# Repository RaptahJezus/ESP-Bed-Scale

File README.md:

ESP Powered Bed Occupancy Sensor

Uses HX711 chip and 4 load cells 

[Load Cells + HX711](https://www.ebay.com/itm/4pcs-50KG-Body-Load-Cell-Resistance-Strain-Weight-Sensor-HX711-AD-Module/182899653153)

Note: Load cells require a bracket that supports the edge, while allowing the middle portion to deflect. Included is "half_bridge_load_sensor_holder-original.stl" which can be 3D printed. I used ABS plastic for mine and it works well.

Load cell bracket design courtesy of linorics on [Thingverse](https://www.thingiverse.com/thing:2486831).

Set up WiFi and MQTT settings in Firmware/include/config.h. Example file is included

Programmed using VSCode + PlatformIO. Schematic designed in EagleCAD

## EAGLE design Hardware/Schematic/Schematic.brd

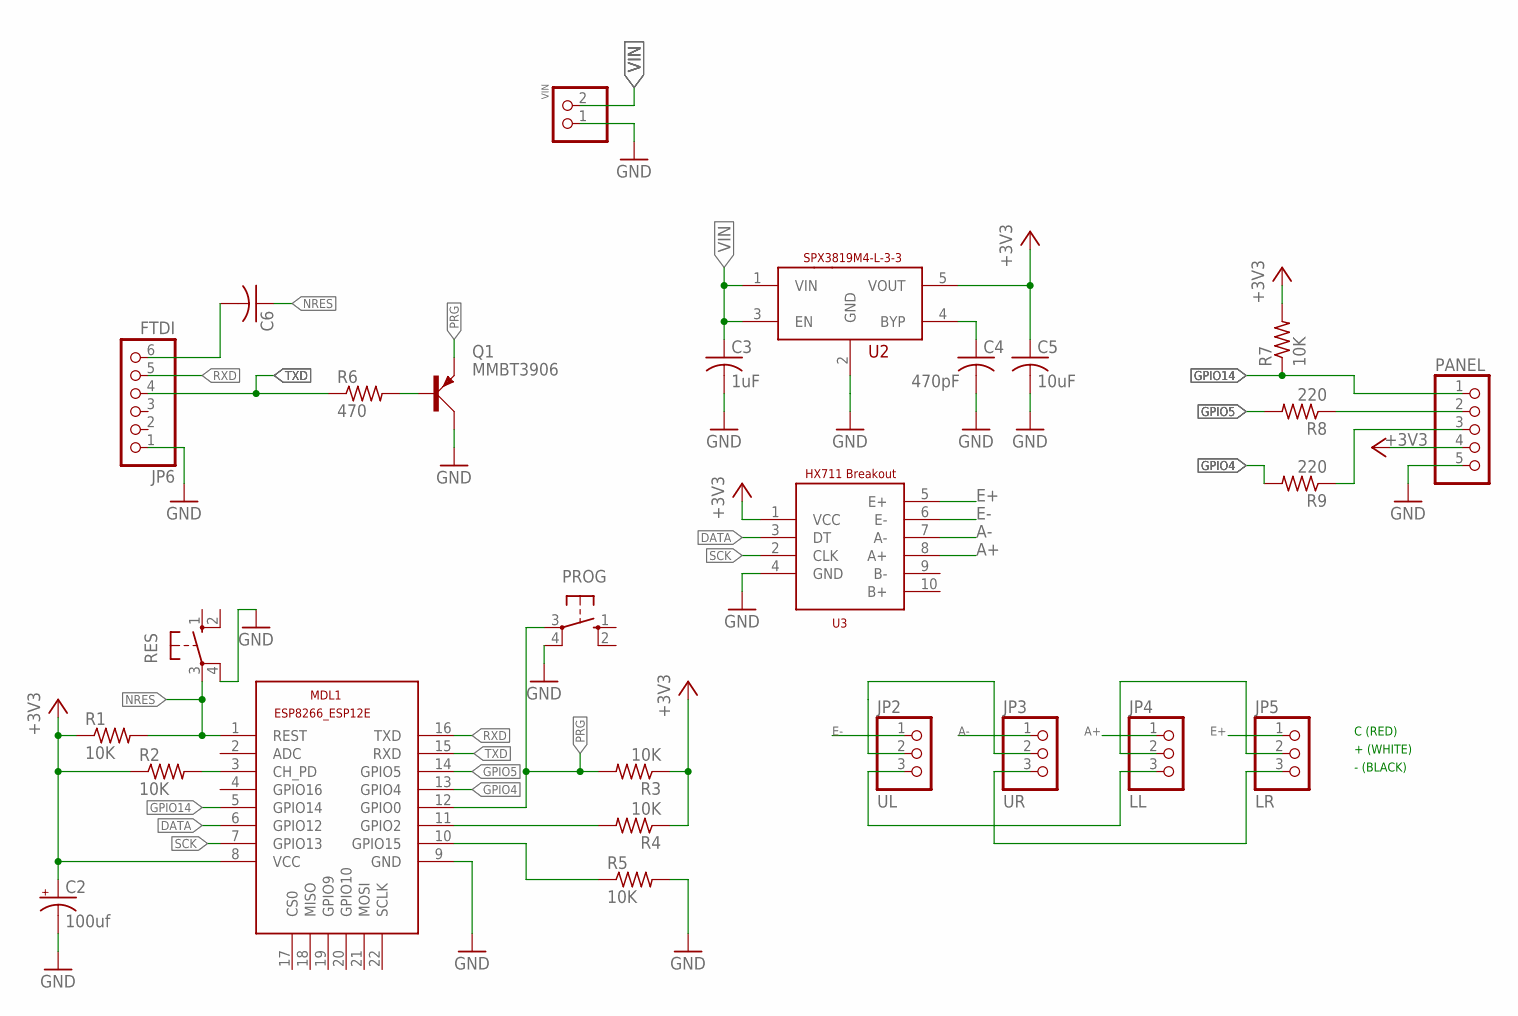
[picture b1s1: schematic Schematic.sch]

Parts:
C2: 100uf; E2,5-6E
C3: 1uF; C0805
C4: 470pF; C0805
C5: 10uF; C0805
C6: 100uF; C025-024X044
JP2: UL; 1X03
JP3: UR; 1X03
JP4: LL; 1X03
JP5: LR; 1X03
JP6: FTDI; 1X06
MDL1: ESP8266-12EESP8266-ESP12E; ESP8266-ESP12E
PANEL: PINHD-1X5; 1X05
PROG: 10-XX; B3F-10XX
Q1: MMBT3906; TO92D
R1, R2, R3, R4, R5, R7: 10K; R0805
R6: 470; R0805
R8, R9: 220; R0805
RES: 10-XX; B3F-10XX
U2: SPX3819M5-L-3-3; SOT23-5L
U3: HX711-BREAKOUT; HX711-THT
VIN: PINHD-1X2; 1X02

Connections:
+3V3: C2.+, C5.1, MDL1.8 (VCC), PANEL.4, R1.1, R2.1, R3.1, R4.1, R7.2, U2.5 (VOUT), U3.1 (VCC)
A+: JP4.1, U3.8 (A+)
A-: JP3.1, U3.7 (A-)
DATA: MDL1.6 (GPIO12), U3.3 (DT)
DTR: C6.2, JP6.6
E+: JP5.1, U3.5 (E+)
E-: JP2.1, U3.6 (E-)
GND: C2.-, C3.2, C4.2, C5.2, JP6.1, MDL1.9 (GND), PANEL.5, PROG.4 (P1), Q1.C, R5.2, RES.4 (P1), U2.2 (GND), U3.4 (GND), VIN.1
GPIO4: MDL1.13 (GPIO4), R9.2
GPIO5: MDL1.14 (GPIO5), R8.2
GPIO14: MDL1.5 (GPIO14), PANEL.1, R7.1
unnamed: Q1.B, R6.2
unnamed: MDL1.3 (CH_PD), R2.2
unnamed: MDL1.10 (GPIO15), R5.1
unnamed: MDL1.11 (GPIO2), R4.2
unnamed: JP2.3, JP4.3
unnamed: JP3.3, JP5.3
unnamed: JP2.2, JP3.2
unnamed: JP4.2, JP5.2
unnamed: C4.1, U2.4 (BYP)
unnamed: PANEL.2, R8.1
unnamed: PANEL.3, R9.1
NRES: C6.1, MDL1.1 (REST), R1.2, RES.3
PRG: MDL1.12 (GPIO0), PROG.3, Q1.E, R3.2
RXD: JP6.5, MDL1.16 (TXD)
SCK: MDL1.7 (GPIO13), U3.2 (CLK)
TXD: JP6.4, MDL1.15 (RXD), R6.1
VIN: C3.1, U2.1 (VIN), U2.3 (EN), VIN.2

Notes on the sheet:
C (RED)
+ (WHITE)
- (BLACK)

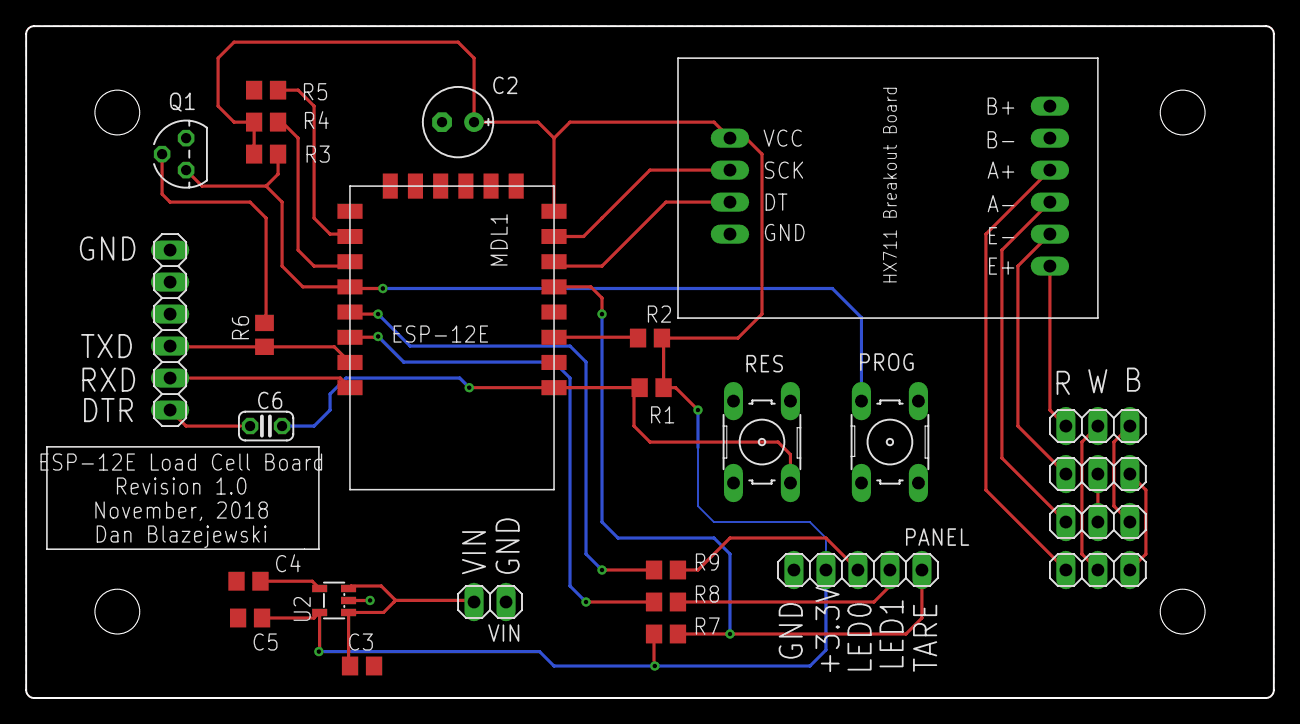
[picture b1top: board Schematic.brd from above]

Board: 2 copper layers, 99.1 x 53.3 mm, 27 parts (0 on the bottom side), 28 nets.

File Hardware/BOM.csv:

"Qty","Value","Part Num","Package","Parts"
"2","","*","B3F-10XX","PROG, RES"
"1","","*","ESP8266-ESP12E","MDL1"
"1","","*","1X02","VIN"
"1","","*","1X05","PANEL"
"1","1uF","*","C0805","C3"
"6","10K","*","R0805","R1, R2, R3, R4, R5, R7"
"1","10uF","*","C0805","C5"
"1","100uf","*","C0805","C1"
"1","100uf","*","E2,5-6E","C2"
"2","220","*","R0805","R8, R9"
"1","470","*","R0805","R6"
"1","470pF","*","C0805","C4"
"1","FTDI","*","1X06","JP6"
"1","HX711-BREAKOUT","*","HX711-THT","U3"
"1","LL","*","1X03","JP4"
"1","LR","*","1X03","JP5"
"1","MMBT3906","*","TO92D","Q1"
"1","SPX3819M5-L-3-3","*","SOT23-5L","U2"
"1","UL","*","1X03","JP2"
"1","UR","*","1X03","JP3"

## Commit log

2020-01-06 Restructured files
2020-01-06 Added hardware files
2020-01-06 Added MQTT output of raw mass (not rounded down to 0.0) for debugging
